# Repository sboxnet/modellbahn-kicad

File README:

modellbahn-kicad

KICAD schemas and Pcbs for modellbahn.

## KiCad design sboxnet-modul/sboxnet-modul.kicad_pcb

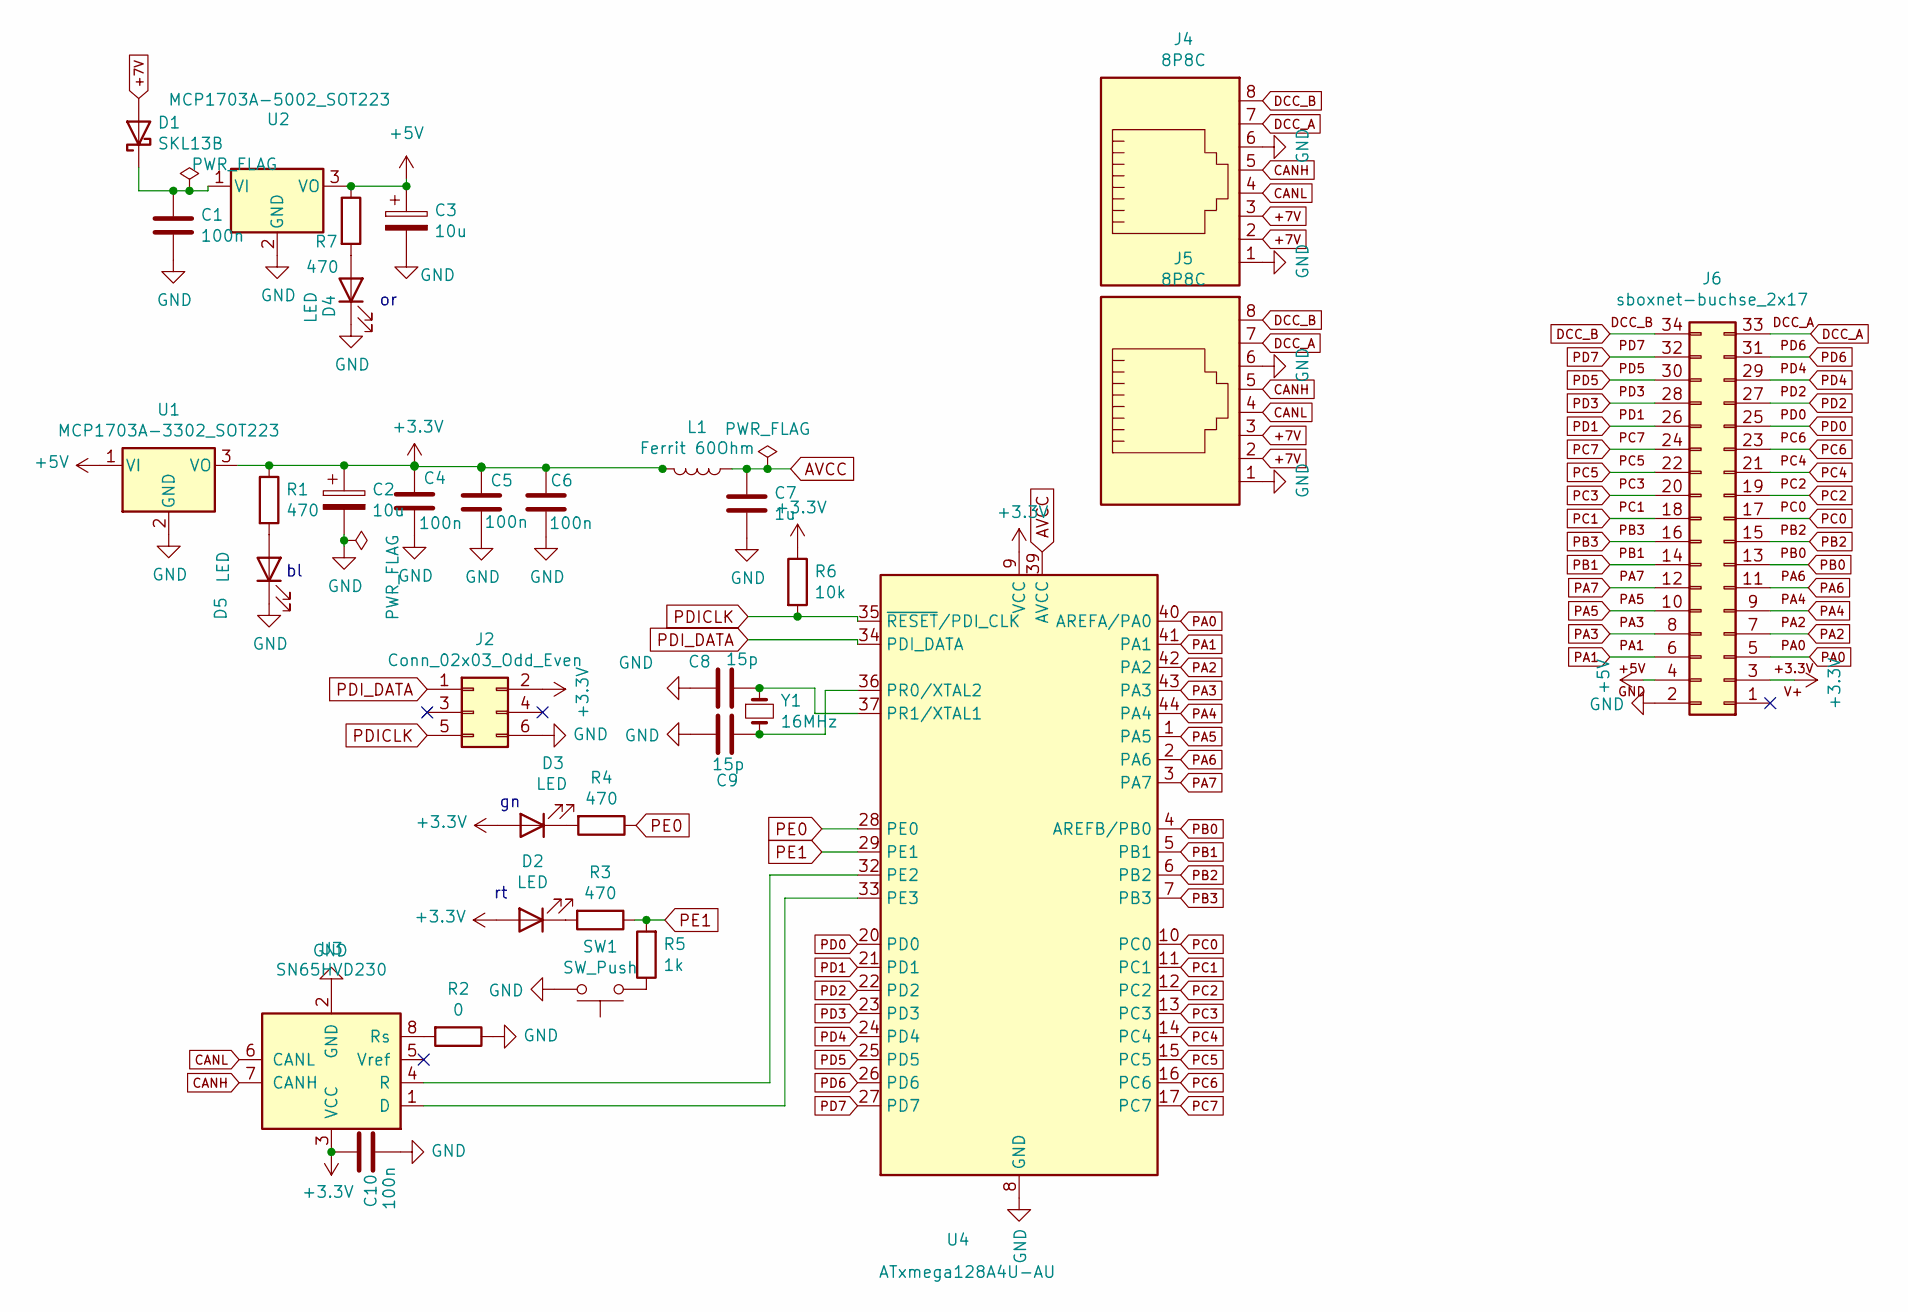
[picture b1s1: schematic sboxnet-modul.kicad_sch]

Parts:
C1, C4, C5, C6, C10: 100n; C_1206_3216Metric_Pad1.33x1.80mm_HandSolder
C2, C3: 10u; C_1206_3216Metric_Pad1.33x1.80mm_HandSolder
C7: 1u; C_1206_3216Metric_Pad1.33x1.80mm_HandSolder
C8, C9: 15p; C_1206_3216Metric_Pad1.33x1.80mm_HandSolder
D1: SKL13B; D_SMB_Handsoldering
D2, D3, D4, D5: LED; LED_1206_3216Metric_Pad1.42x1.75mm_HandSolder
J2: Conn_02x03_Odd_Even; wannenstecker_gerade_6pin
J4, J5: 8P8C; 8p8c-mebp
J6: sboxnet-buchse_2x17; sboxnet-buchse-2x17
L1: Ferrit 60Ohm; L_1206_3216Metric_Pad1.42x1.75mm_HandSolder
R1, R3, R4, R7: 470; R_1206_3216Metric_Pad1.30x1.75mm_HandSolder
R2: 0; R_1206_3216Metric_Pad1.30x1.75mm_HandSolder
R5: 1k; R_1206_3216Metric_Pad1.30x1.75mm_HandSolder
R6: 10k; R_1206_3216Metric_Pad1.30x1.75mm_HandSolder
SW1: SW_Push; JTP-1130
U1: MCP1703A-3302_SOT223; SOT-223-3_TabPin2
U2: MCP1703A-5002_SOT223; SOT-223-3_TabPin2
U3: SN65HVD230; SOIC-8_3.9x4.9mm_P1.27mm
U4: ATxmega128A4U-AU; TQFP-44_10x10mm_P0.8mm
Y1: 16MHz; Crystal_HC49-U_Vertical

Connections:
+3.3V: C2.1, C4.2, C5.2, C6.2, C10.2, D2.2 (A), D3.2 (A), J2.2, J6.3, L1.2, R1.1, R6.1, U1.3 (VO), U3.3 (VCC), U4.9 (VCC), U4.19 (VCC), U4.31 (VCC); also elsewhere on the board
+5V: C3.1, J6.4, R7.1, U1.1 (VI), U2.3 (VO); also elsewhere on the board
+7V: D1.2 (A), J4.2, J4.3, J5.2, J5.3
+V: J6.1
AVCC: C7.2, L1.1, U4.39 (AVCC)
CANH: J4.5, J5.5, U3.7 (CANH)
CANL: J4.4, J5.4, U3.6 (CANL)
DCC_A: J4.7, J5.7, J6.33
DCC_B: J4.8, J5.8, J6.34
GND: C1.1, C2.2, C3.2, C4.1, C5.1, C6.1, C7.1, C8.2, C9.2, C10.1, D4.1 (K), D5.1 (K), J2.6, J4.1, J4.6, J5.1, J5.6, J6.2, R2.1, SW1.2, U1.2 (GND), U2.2 (GND), U3.2 (GND), U4.8 (GND), U4.18 (GND), U4.30 (GND), U4.38 (GND); also elsewhere on the board
unnamed 10: C1.2, D1.1 (K), U2.1 (VI); also elsewhere on the board
unnamed: C8.1, U4.37 (PR1/XTAL1), Y1.1
unnamed: C9.1, U4.36 (PR0/XTAL2), Y1.2
unnamed: D2.1 (K), R3.2
unnamed: D3.1 (K), R4.2
unnamed: D4.2 (A), R7.2
unnamed: D5.2 (A), R1.2
unnamed: R2.2, U3.8 (Rs)
unnamed: R5.1, SW1.1
unnamed: U3.1 (D), U4.33 (PE3)
unnamed: U3.4 (R), U4.32 (PE2)
PA0: J6.5, U4.40 (AREFA/PA0)
PA1: J6.6, U4.41 (PA1)
PA2: J6.7, U4.42 (PA2)
PA3: J6.8, U4.43 (PA3)
PA4: J6.9, U4.44 (PA4)
PA5: J6.10, U4.1 (PA5)
PA6: J6.11, U4.2 (PA6)
PA7: J6.12, U4.3 (PA7)
PB0: J6.13, U4.4 (AREFB/PB0)
PB1: J6.14, U4.5 (PB1)
PB2: J6.15, U4.6 (PB2)
PB3: J6.16, U4.7 (PB3)
PC0: J6.17, U4.10 (PC0)
PC1: J6.18, U4.11 (PC1)
PC2: J6.19, U4.12 (PC2)
PC3: J6.20, U4.13 (PC3)
PC4: J6.21, U4.14 (PC4)
PC5: J6.22, U4.15 (PC5)
PC6: J6.23, U4.16 (PC6)
PC7: J6.24, U4.17 (PC7)
PD0: J6.25, U4.20 (PD0)
PD1: J6.26, U4.21 (PD1)
PD2: J6.27, U4.22 (PD2)
PD3: J6.28, U4.23 (PD3)
PD4: J6.29, U4.24 (PD4)
PD5: J6.30, U4.25 (PD5)
PD6: J6.31, U4.26 (PD6)
PD7: J6.32, U4.27 (PD7)
PDICLK: J2.5, R6.2, U4.35 (~RESET/PDI_CLK)
PDI_DATA: J2.1, U4.34 (PDI_DATA)
PE0: R4.1, U4.28 (PE0)
PE1: R3.1, R5.2, U4.29 (PE1)

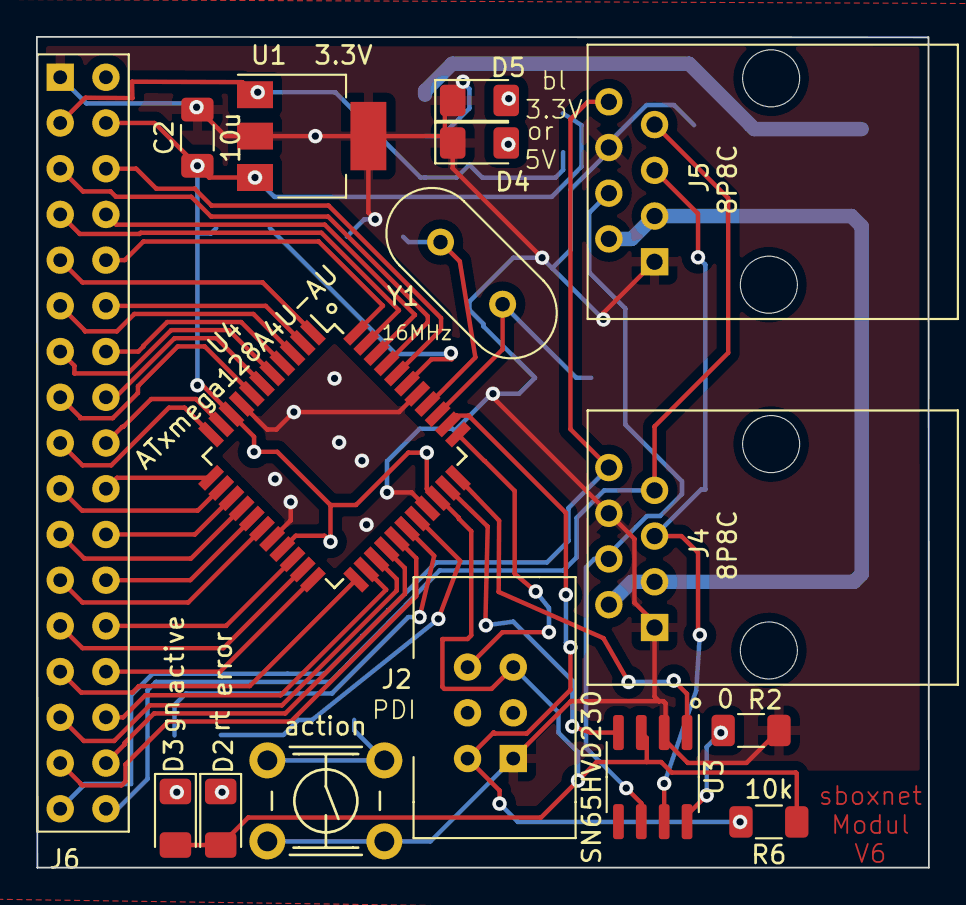
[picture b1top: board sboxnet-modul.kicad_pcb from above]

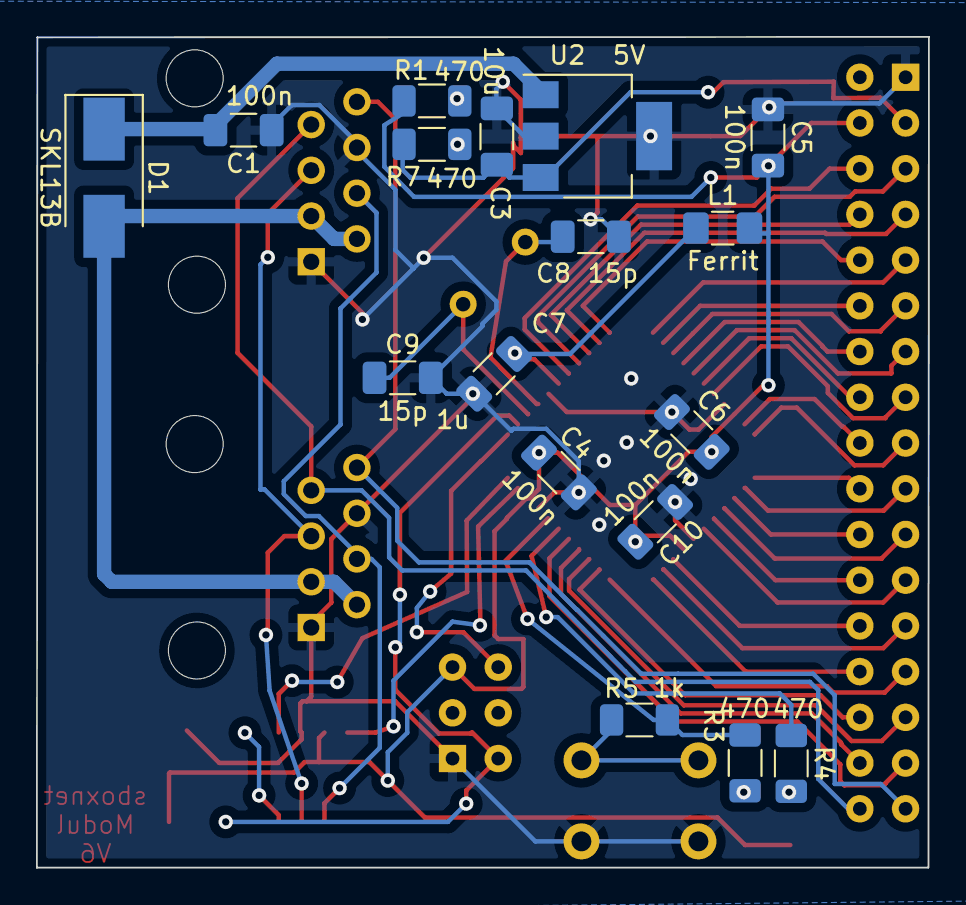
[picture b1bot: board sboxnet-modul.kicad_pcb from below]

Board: 2 copper layers, 49.6 x 46.2 mm, 33 parts (17 on the bottom side), 52 nets.

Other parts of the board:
U1  3.3V: MCP1703A-3302_SOT223; SOT-223-3_TabPin2
U2  5V: MCP1703A-5002_SOT223; SOT-223-3_TabPin2

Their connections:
+3.3V: U1 3.3V.3 (VO); also elsewhere on the board
+5V: U1 3.3V.1 (VI), U2 5V.3 (VO); also elsewhere on the board
GND: U1 3.3V.2 (GND), U2 5V.2 (GND); also elsewhere on the board
unnamed 10: U2 5V.1 (VI); also elsewhere on the board

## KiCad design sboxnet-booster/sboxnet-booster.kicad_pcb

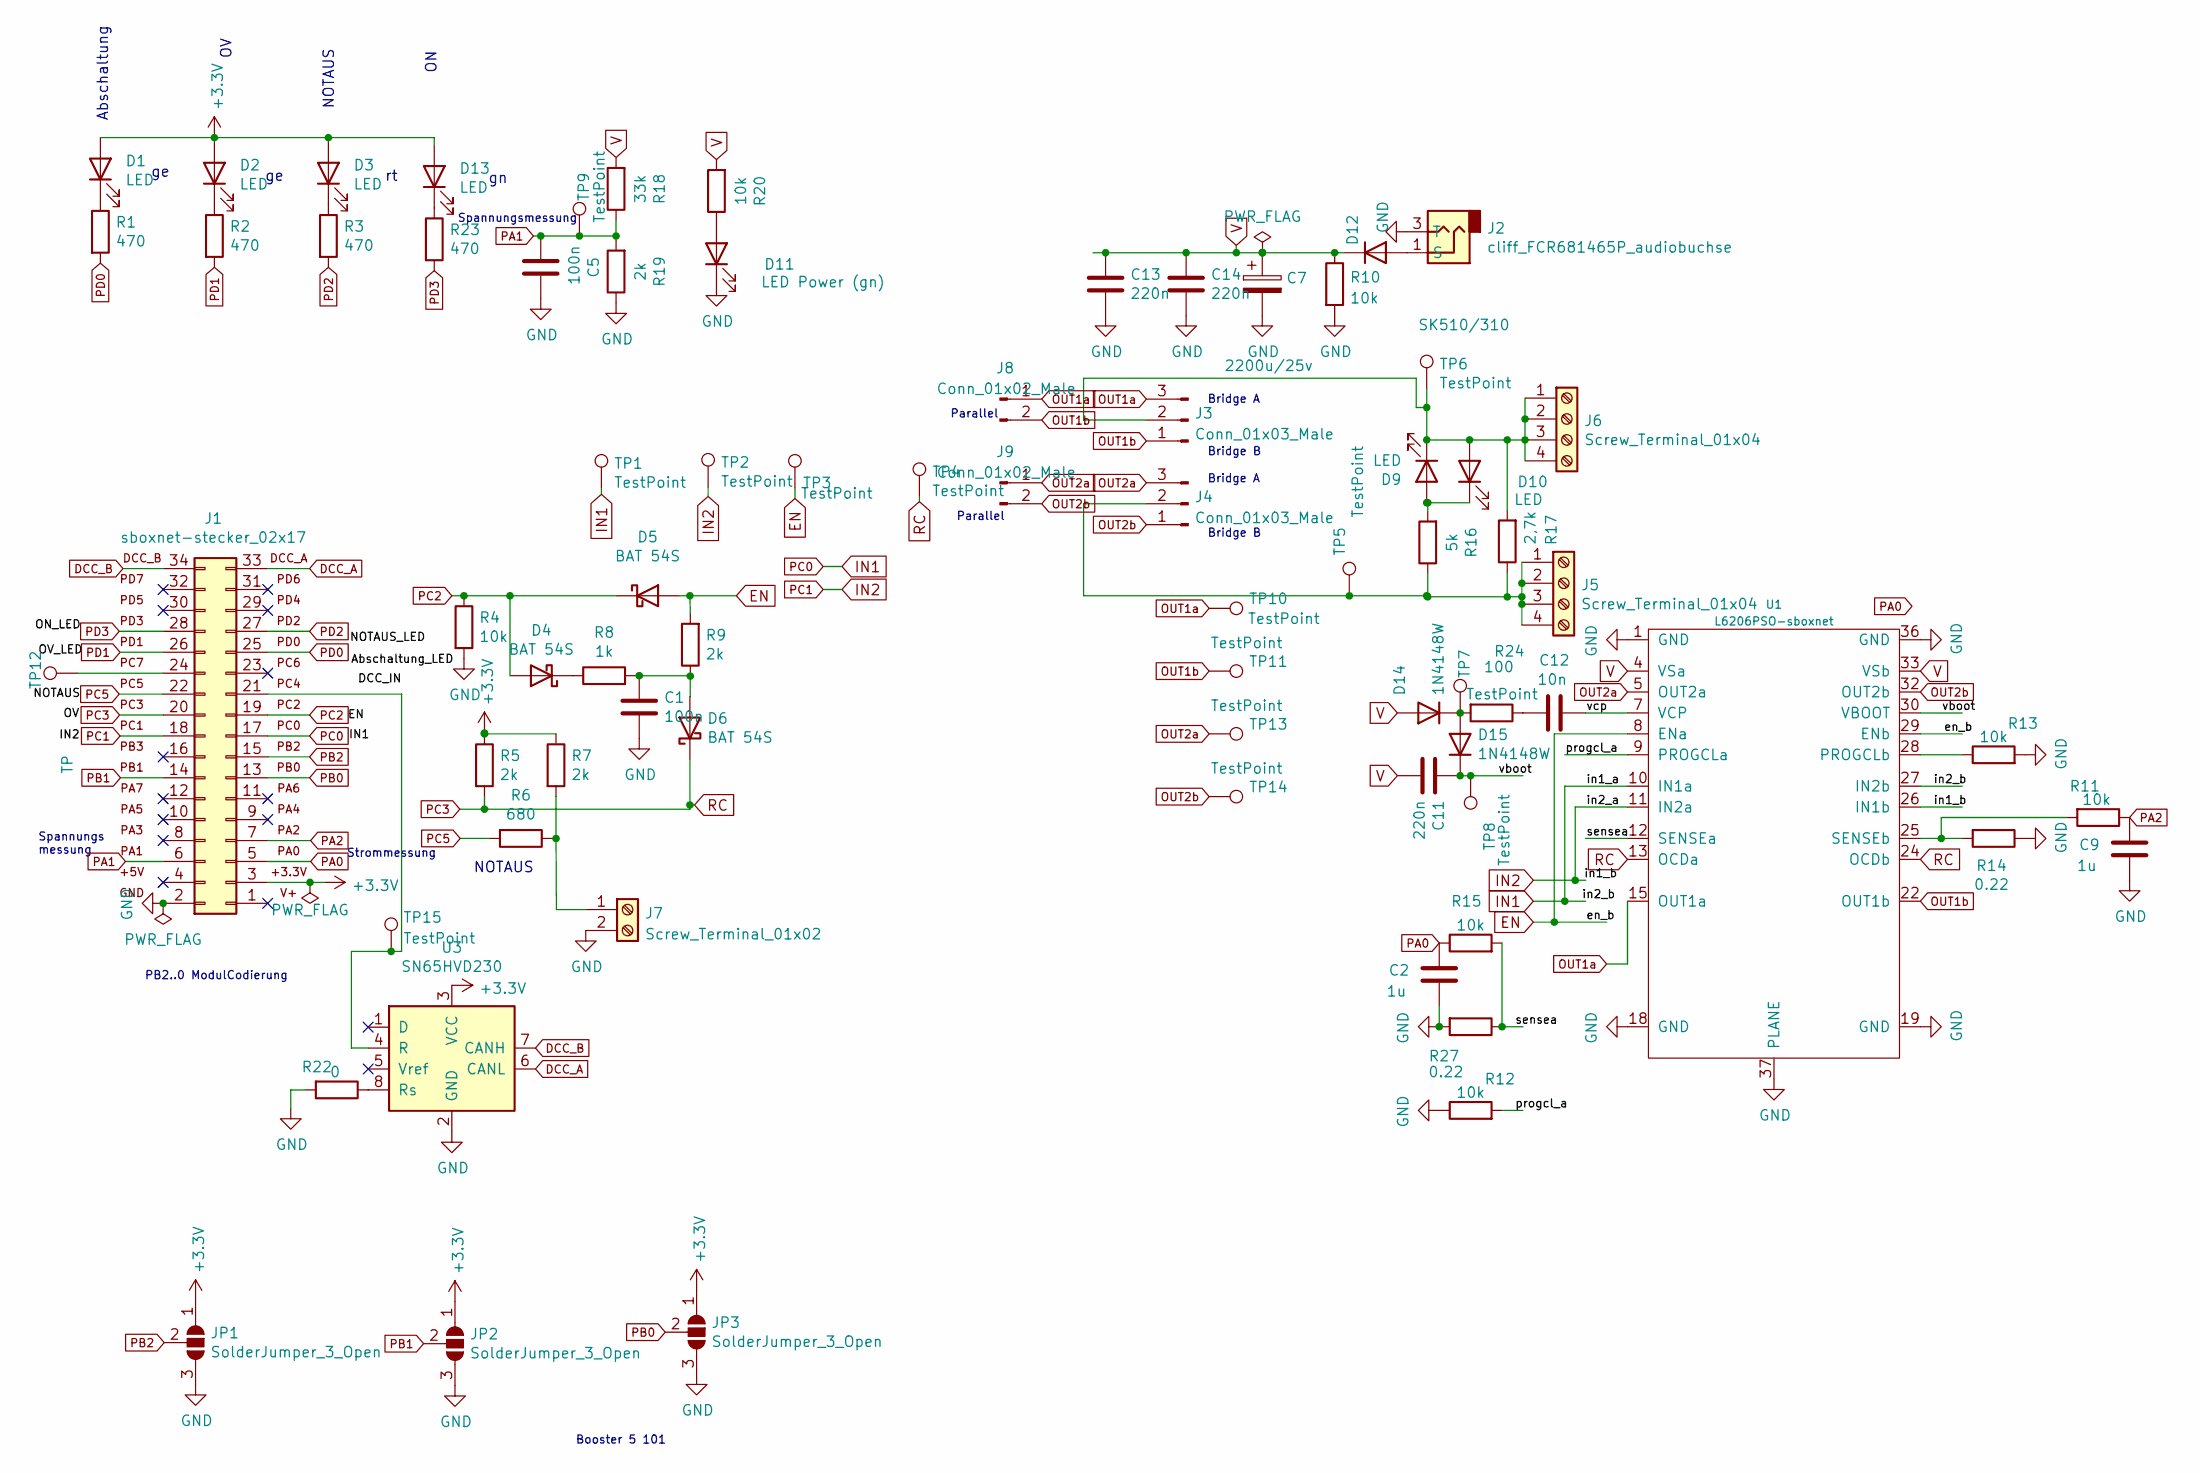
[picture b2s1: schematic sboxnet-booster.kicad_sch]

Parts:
C1, C5: 100n; C_1206_3216Metric
C2, C9: 1u; C_1206_3216Metric
C7: 2200u/25v; CP_Axial_L30.0mm_D15.0mm_P35.00mm_Horizontal
C11, C13, C14: 220n; C_1206_3216Metric
C12: 10n; C_1206_3216Metric
D1, D2, D3, D9, D10, D13: LED; LED_D3.0mm
D4, D5, D6: BAT 54S; SOT-23_Handsoldering
D11: LED Power (gn); LED_D3.0mm
D12: SK510/310; D_SMB_Handsoldering
D14, D15: 1N4148W; D_SOD-123F
J1: sboxnet-stecker_02x17; sboxnet-stecker-2x17
J2: cliff_FCR681465P_audiobuchse; CLIFF-FCR681465P
J3, J4: Conn_01x03_Male; PinHeader_1x03_P2.54mm_Vertical
J5, J6: Screw_Terminal_01x04; TerminalBlock_Altech_AK300-4_P5.00mm
J7: Screw_Terminal_01x02; TerminalBlock_Altech_AK300-2_P5.00mm
J8, J9: Conn_01x02_Male; PinHeader_1x02_P2.54mm_Vertical
JP1, JP2, JP3: SolderJumper_3_Open; SolderJumper-3_P1.3mm_Open_RoundedPad1.0x1.5mm
R1, R2, R3, R23: 470; R_1206_3216Metric_Pad1.30x1.75mm_HandSolder
R4, R10, R11, R12, R13, R15, R20: 10k; R_1206_3216Metric_Pad1.30x1.75mm_HandSolder
R5, R7, R9, R19: 2k; R_1206_3216Metric_Pad1.30x1.75mm_HandSolder
R6: 680; R_1206_3216Metric_Pad1.30x1.75mm_HandSolder
R8: 1k; R_1206_3216Metric_Pad1.30x1.75mm_HandSolder
R14, R27: 0.22; R_Axial_DIN0614_L14.3mm_D5.7mm_P15.24mm_Horizontal
R16: 5k; R_1206_3216Metric_Pad1.30x1.75mm_HandSolder
R17: 2,7k; R_1206_3216Metric_Pad1.30x1.75mm_HandSolder
R18: 33k; R_1206_3216Metric_Pad1.30x1.75mm_HandSolder
R22: 0; R_1206_3216Metric_Pad1.30x1.75mm_HandSolder
R24: 100; R_1206_3216Metric_Pad1.30x1.75mm_HandSolder
TP1, TP2, TP3, TP4, TP5, TP6, TP7, TP8, TP9, TP10, TP11, TP13, TP14, TP15: TestPoint; PinHeader_1x01_P2.54mm_Vertical
TP12: TP; PinHeader_1x01_P2.54mm_Vertical
U1: L6206PSO-sboxnet; HSOP-36-1EP_11.0x15.9mm_P0.65mm_SlugDown_ThermalVias
U3: SN65HVD230; SOIC-8_3.9x4.9mm_P1.27mm

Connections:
+3V3: D1.2 (A), D2.2 (A), D3.2 (A), D13.2 (A), J1.3, JP1.1 (A), JP2.1 (A), JP3.1 (A), R5.1, R7.1, U3.3 (VCC)
/progcl_a: R12.2, U1.9 (PROGCLa)
/sensea: R15.2, R27.1, U1.12 (SENSEa)
/vboot: C11.2, D15.1 (K), TP8.1, U1.30 (VBOOT)
/vcp: C12.1, U1.7 (VCP)
DCC_A: J1.33, U3.6 (CANL)
DCC_B: J1.34, U3.7 (CANH)
EN: D5.1 (A), R9.2, TP3.1, U1.8 (ENa), U1.29 (ENb)
GND: C1.2, C2.1, C5.1, C7.2, C9.1, C13.1, C14.1, D11.1 (K), J1.2, J2.3 (T), J7.2, JP1.3 (B), JP2.3 (B), JP3.3 (B), R4.2, R10.2, R12.1, R13.2, R14.1, R19.1, R22.2, R27.2, U1.1 (GND), U1.18 (GND), U1.19 (GND), U1.36 (GND), U1.37 (PLANE), U3.2 (GND)
unnamed: C1.1, D6.1 (A), R8.2, R9.1
unnamed: C12.2, R24.1
unnamed: D1.1 (K), R1.1
unnamed: D2.1 (K), R2.1
unnamed: D3.1 (K), R3.1
unnamed: D4.3 (K), R8.1
unnamed: D9.2 (A), D10.1 (K), R16.2
unnamed: D9.1 (K), D10.2 (A), J3.2, J6.1, J6.2, J6.3, J6.4, R17.2, TP6.1
unnamed: D11.2 (A), R20.1
unnamed: D12.2 (A), J2.1 (S)
unnamed: D13.1 (K), R23.1
unnamed: D14.1 (K), D15.2 (A), R24.2, TP7.1
unnamed: J1.21, TP15.1, U3.4 (R)
unnamed: J1.24, TP12.1
unnamed: J4.2, J5.1, J5.2, J5.3, J5.4, R16.1, R17.1, TP5.1
unnamed: J7.1, R6.1, R7.2
unnamed: R11.2, R14.2, U1.25 (SENSEb)
unnamed: R13.1, U1.28 (PROGCLb)
unnamed: R22.1, U3.8 (Rs)
OUT1a: J3.3, J8.1, TP10.1, U1.15 (OUT1a)
OUT1b: J3.1, J8.2, TP11.1, U1.22 (OUT1b)
OUT2a: J4.3, J9.1, TP13.1, U1.5 (OUT2a)
OUT2b: J4.1, J9.2, TP14.1, U1.32 (OUT2b)
PA0: C2.2, J1.5, R15.1
PA1: C5.2, J1.6, R18.1, R19.2, TP9.1
PA2: C9.2, J1.7, R11.1
PB0: J1.13, JP3.2 (C)
PB1: J1.14, JP2.2 (C)
PB2: J1.15, JP1.2 (C)
PC2: D4.1 (A), D5.3 (K), J1.19, R4.1
PC3: D6.3 (K), J1.20, R5.2, TP4.1, U1.13 (OCDa), U1.24 (OCDb)
PC5: J1.22, R6.2
PD0: J1.25, R1.2
PD1: J1.26, R2.2
PD2: J1.27, R3.2
PD3: J1.28, R23.2
V: C7.1, C11.1, C13.2, C14.2, D12.1 (K), D14.2 (A), R10.1, R18.2, R20.2, U1.4 (VSa), U1.33 (VSb)

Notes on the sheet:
NOTAUS
Bridge B
Abschaltung
Bridge A
Booster 5 101
Spannungs messung
Spannungsmessung
Strommessung
Parallel
PB2..0 ModulCodierung

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
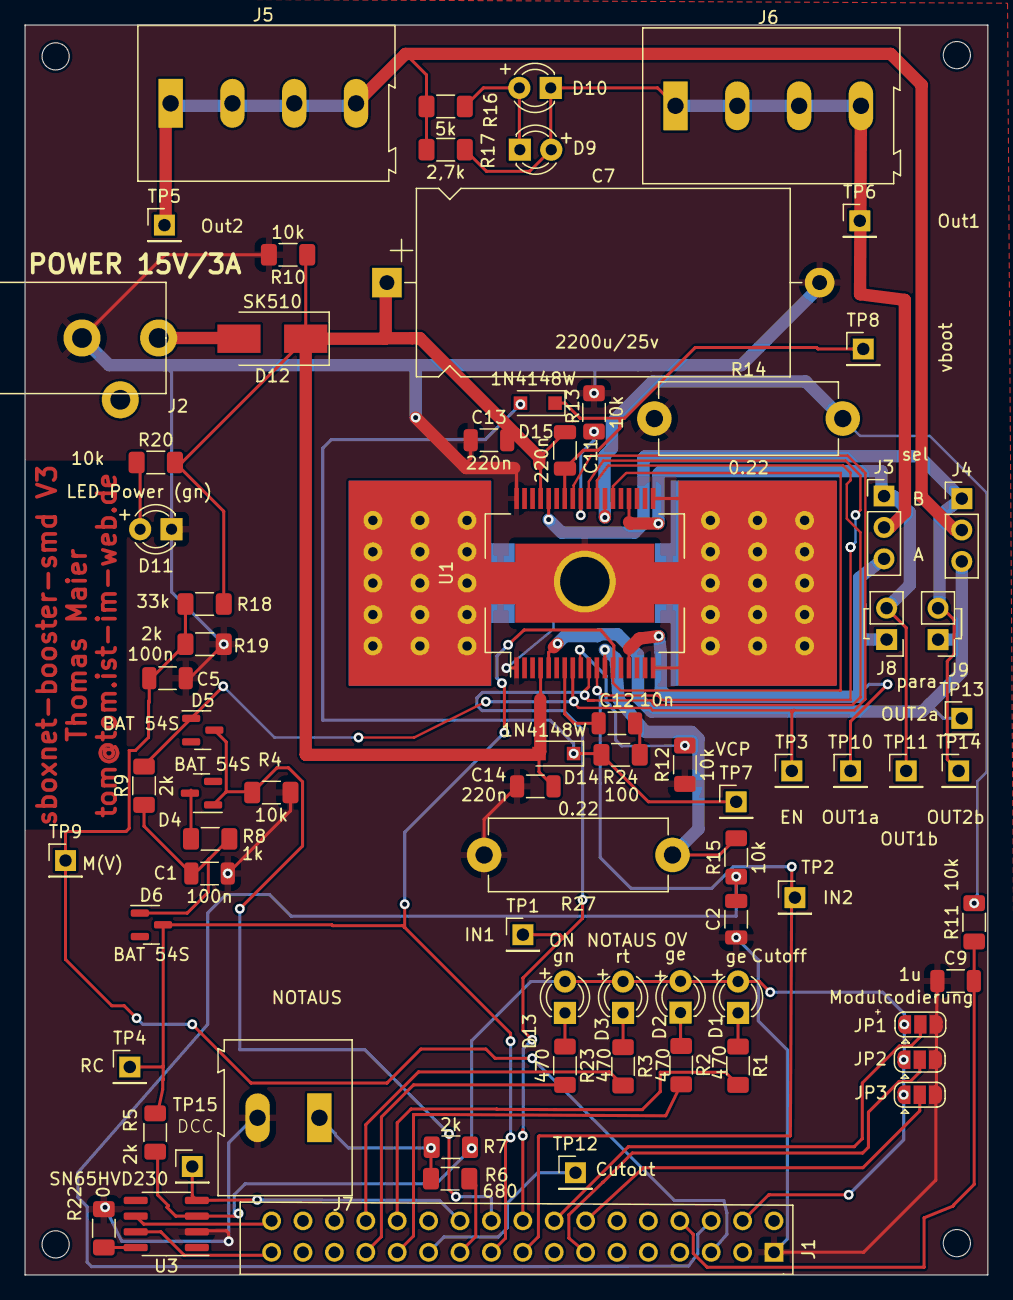
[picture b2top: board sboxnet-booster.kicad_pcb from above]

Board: 2 copper layers, 77.9 x 101.1 mm, 75 parts (0 on the bottom side), 48 nets.

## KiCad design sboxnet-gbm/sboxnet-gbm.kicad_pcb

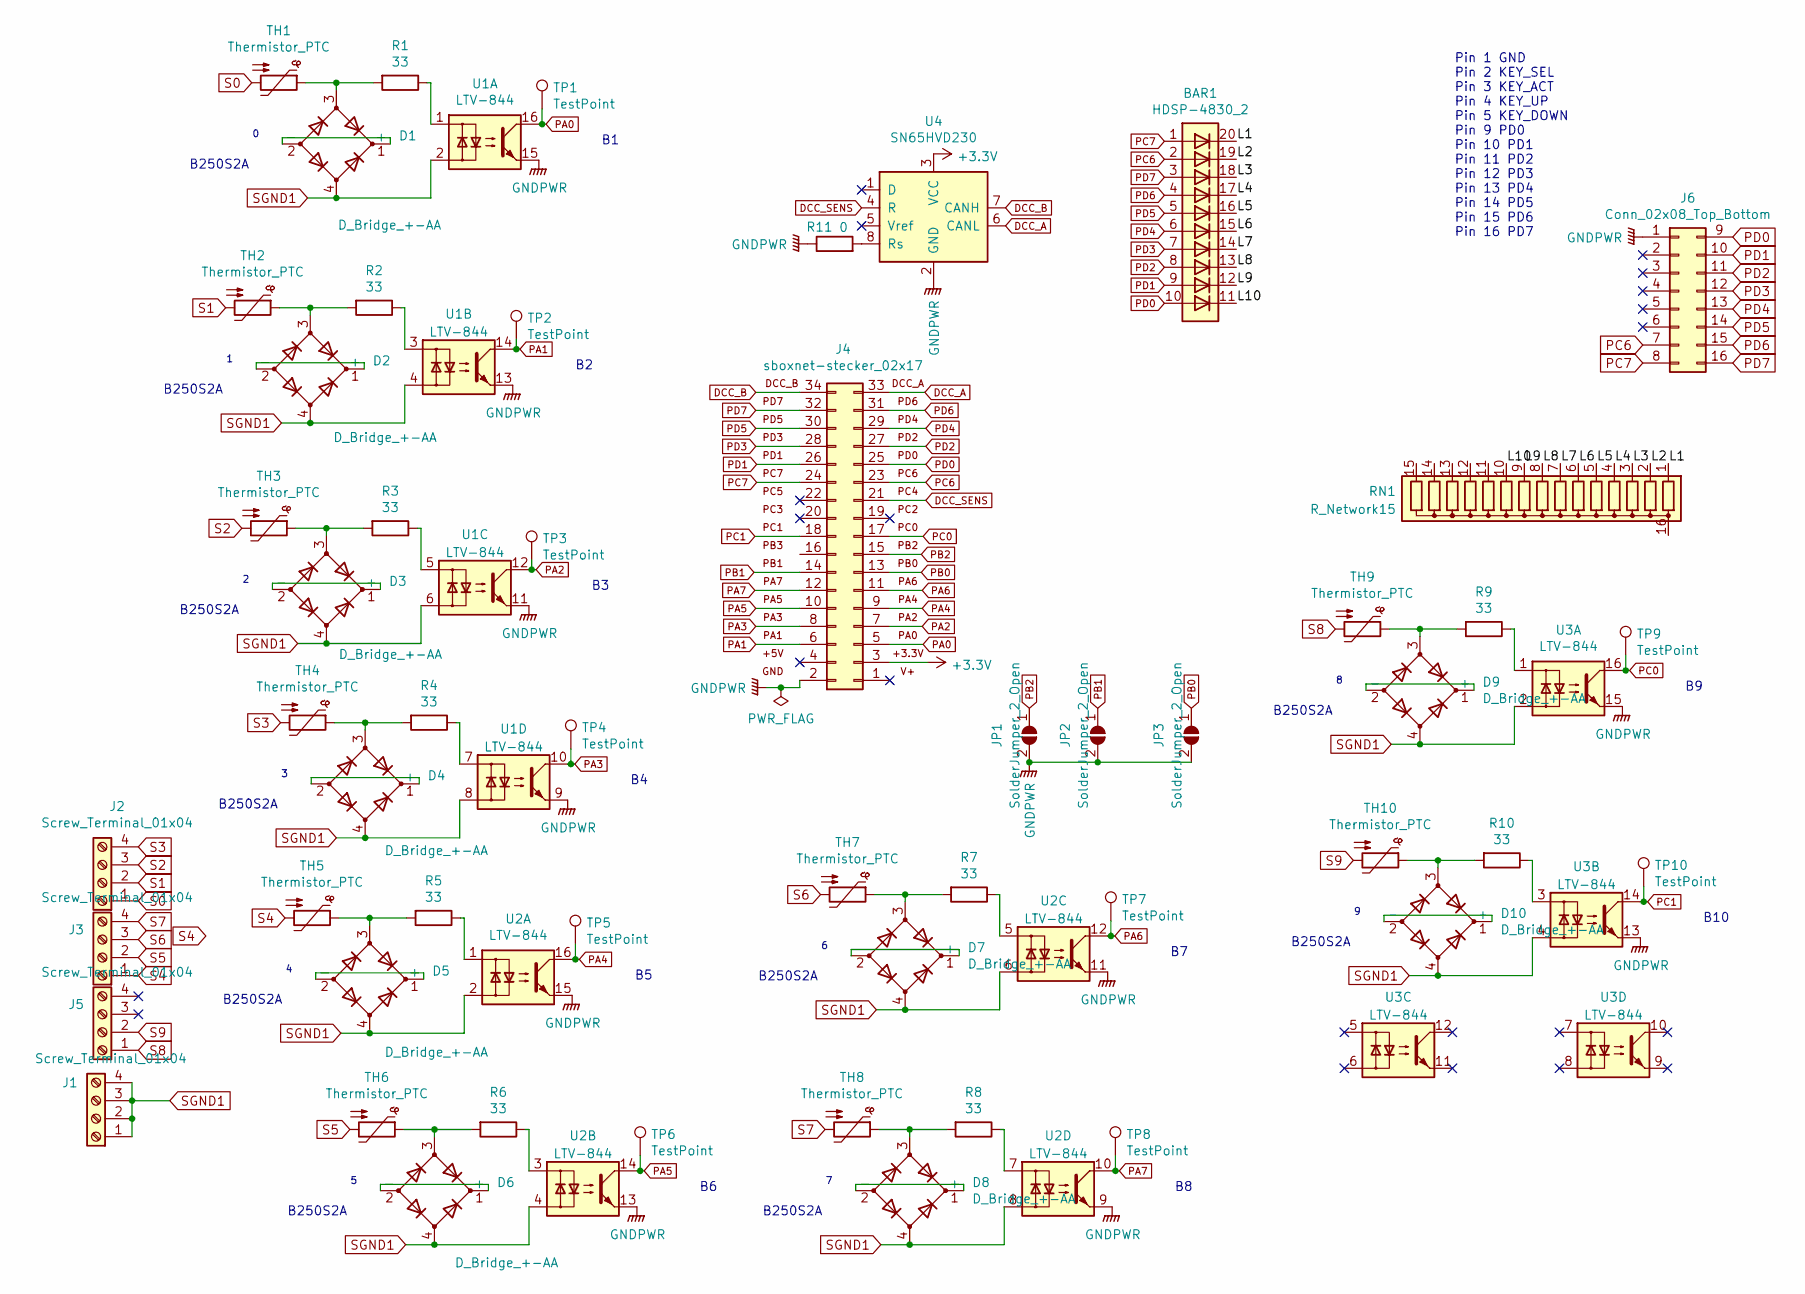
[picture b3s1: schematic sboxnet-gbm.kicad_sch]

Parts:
BAR1: HDSP-4830_2; DIP-20_W7.62mm_Socket
D1, D2, D3, D4, D5, D6, D7, D8, D9, D10: D_Bridge_+-AA; Diode_Bridge_Diotec_SO-DIL-Slim
J1, J2, J3, J5: Screw_Terminal_01x04; TerminalBlock_Altech_AK300-4_P5.00mm
J4: sboxnet-stecker_02x17; sboxnet-stecker-2x17
J6: Conn_02x08_Top_Bottom; PinSocket_2x08_P2.54mm_Vertical
JP1, JP2, JP3: SolderJumper_2_Open; SolderJumper-2_P1.3mm_Open_TrianglePad1.0x1.5mm
R1, R2, R3, R4, R5, R6, R7, R8, R9, R10: 33; R_1206_3216Metric_Pad1.30x1.75mm_HandSolder
R11: 0; R_1206_3216Metric_Pad1.30x1.75mm_HandSolder
RN1: R_Network15; SOIC-16W_5.3x10.2mm_P1.27mm
TH1, TH2, TH3, TH4, TH5, TH6, TH7, TH8, TH9, TH10: Thermistor_PTC; R_1206_3216Metric
TP1, TP2, TP3, TP4, TP5, TP6, TP7, TP8, TP9, TP10: TestPoint; PinHeader_1x01_P2.54mm_Vertical
U1, U2, U3: LTV-844; SOIC-16_4.55x10.3mm_P1.27mm
U4: SN65HVD230; SOIC-8_3.9x4.9mm_P1.27mm

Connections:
+3V3: J4.3, U4.3 (VCC)
/L1: BAR1.20 (K), RN1.1 (R1)
/L2: BAR1.19 (K), RN1.2 (R2)
/L3: BAR1.18 (K), RN1.3 (R3)
/L4: BAR1.17 (K), RN1.4 (R4)
/L5: BAR1.16 (K), RN1.5 (R5)
/L6: BAR1.15 (K), RN1.6 (R6)
/L7: BAR1.14 (K), RN1.7 (R7)
/L8: BAR1.13 (K), RN1.8 (R8)
/L9: BAR1.12 (K), RN1.9 (R9)
/L10: BAR1.11 (K), RN1.10 (R10)
DCC_A: J4.33, U4.6 (CANL)
DCC_B: J4.34, U4.7 (CANH)
DCC_SENS: J4.21, U4.4 (R)
GNDPWR: J4.2, J6.1, JP1.2 (B), JP2.2 (B), JP3.2 (B), R11.1, U1.9, U1.11, U1.13, U1.15, U2.9, U2.11, U2.13, U2.15, U3.13, U3.15, U4.2 (GND)
unnamed: D1.1 (+), D1.2 (-)
unnamed: D1.3, R1.2, TH1.1
unnamed: D2.1 (+), D2.2 (-)
unnamed: D2.3, R2.2, TH2.1
unnamed: D3.1 (+), D3.2 (-)
unnamed: D3.3, R3.2, TH3.1
unnamed: D4.1 (+), D4.2 (-)
unnamed: D4.3, R4.2, TH4.1
unnamed: D5.1 (+), D5.2 (-)
unnamed: D5.3, R5.2, TH5.1
unnamed: D6.1 (+), D6.2 (-)
unnamed: D6.3, R6.2, TH6.1
unnamed: D7.1 (+), D7.2 (-)
unnamed: D7.3, R7.2, TH7.1
unnamed: D8.1 (+), D8.2 (-)
unnamed: D8.3, R8.2, TH8.1
unnamed: D9.1 (+), D9.2 (-)
unnamed: D9.3, R9.2, TH9.1
unnamed: D10.1 (+), D10.2 (-)
unnamed: D10.3, R10.2, TH10.1
unnamed: R1.1, U1.1
unnamed: R2.1, U1.3
unnamed: R3.1, U1.5
unnamed: R4.1, U1.7
unnamed: R5.1, U2.1
unnamed: R6.1, U2.3
unnamed: R7.1, U2.5
unnamed: R8.1, U2.7
unnamed: R9.1, U3.1
unnamed: R10.1, U3.3
unnamed: R11.2, U4.8 (Rs)
PA0: J4.5, TP1.1, U1.16
PA1: J4.6, TP2.1, U1.14
PA2: J4.7, TP3.1, U1.12
PA3: J4.8, TP4.1, U1.10
PA4: J4.9, TP5.1, U2.16
PA5: J4.10, TP6.1, U2.14
PA6: J4.11, TP7.1, U2.12
PA7: J4.12, TP8.1, U2.10
PB0: J4.13, JP3.1 (A)
PB1: J4.14, JP2.1 (A)
PB2: J4.15, JP1.1 (A)
PC0: J4.17, TP9.1, U3.16
PC1: J4.18, TP10.1, U3.14
PC6: BAR1.2 (A), J4.23, J6.7
PC7: BAR1.1 (A), J4.24, J6.8
PD0: BAR1.10 (A), J4.25, J6.9
PD1: BAR1.9 (A), J4.26, J6.10
PD2: BAR1.8 (A), J4.27, J6.11
PD3: BAR1.7 (A), J4.28, J6.12
PD4: BAR1.6 (A), J4.29, J6.13
PD5: BAR1.5 (A), J4.30, J6.14
PD6: BAR1.4 (A), J4.31, J6.15
PD7: BAR1.3 (A), J4.32 (PD7), J6.16
S0: J2.1, TH1.2
S1: J2.2, TH2.2
S2: J2.3, TH3.2
S3: J2.4, TH4.2
S4: J3.1, TH5.2
S5: J3.2, TH6.2
S6: J3.3, TH7.2
S7: J3.4, TH8.2
S8: J5.1, TH9.2
S9: J5.2, TH10.2
SGND1: D1.4, D2.4, D3.4, D4.4, D5.4, D6.4, D7.4, D8.4, D9.4, D10.4, J1.1, J1.2, J1.3, J1.4, U1.2, U1.4, U1.6, U1.8, U2.2, U2.4, U2.6, U2.8, U3.2, U3.4

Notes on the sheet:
B250S2A
Pin 1 GND Pin 2 KEY_SEL Pin 3 KEY_ACT Pin 4 KEY_UP Pin 5 KEY_DOWN Pin 9 PD0 Pin 10 PD1 Pin 11 PD2 Pin 12 PD3 Pin 13 PD4 Pin 14 PD5 Pin 15 PD6 Pin 16 PD7
B10

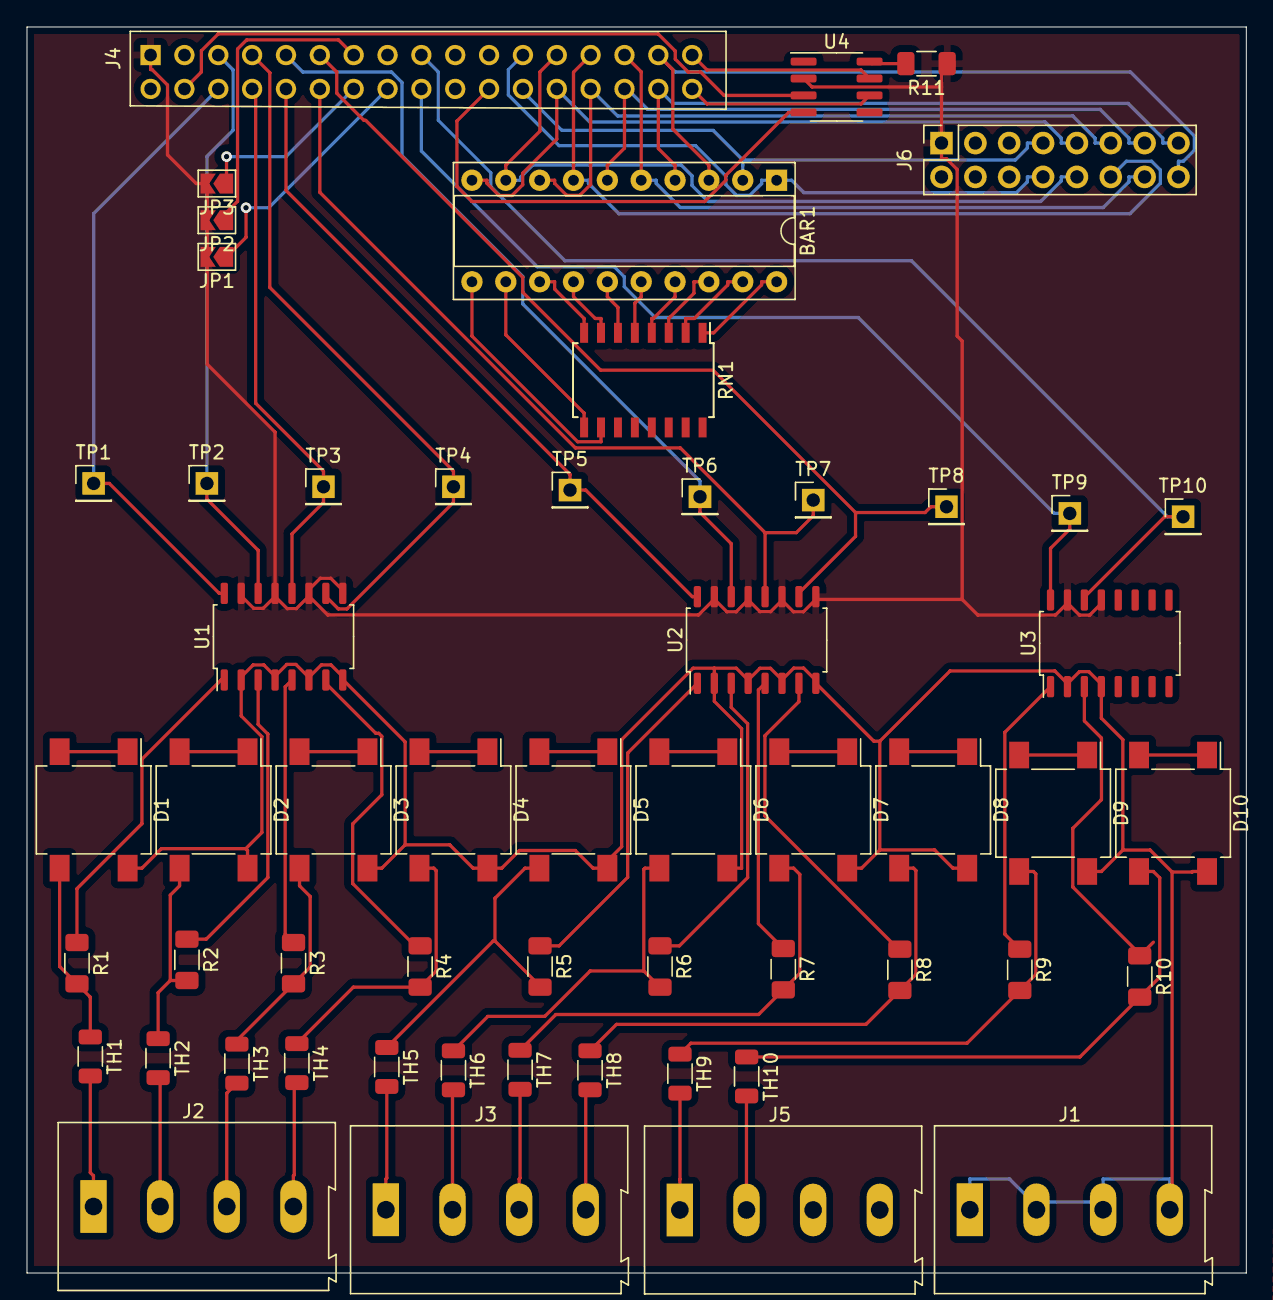
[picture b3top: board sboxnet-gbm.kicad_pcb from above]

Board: 2 copper layers, 91.5 x 93.5 mm, 56 parts (0 on the bottom side), 80 nets.

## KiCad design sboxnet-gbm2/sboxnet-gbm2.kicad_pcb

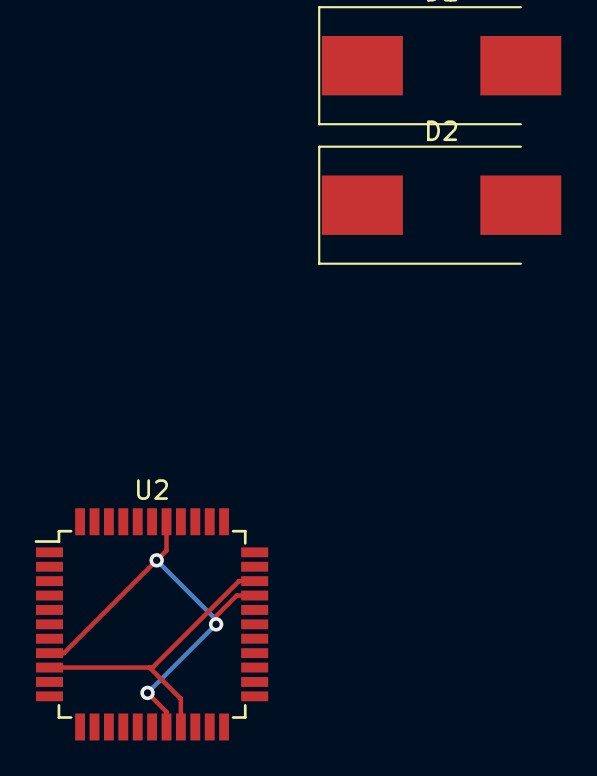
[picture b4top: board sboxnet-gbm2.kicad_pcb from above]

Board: 2 copper layers, 3 parts (0 on the bottom side), 3 nets.

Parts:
D1, D2: SB340; D_SMC_Handsoldering
U2: ATxmega32A4U-A; TQFP-44_10x10mm_P0.8mm

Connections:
+3.3VP: U2.9 (VCC), U2.19 (VCC), U2.31 (VCC)
/dcc1: D1.2 (A), D2.1 (K)
GND1: D1.1 (K), D2.2 (A), U2.8 (GND), U2.18 (GND), U2.30 (GND), U2.38 (GND)

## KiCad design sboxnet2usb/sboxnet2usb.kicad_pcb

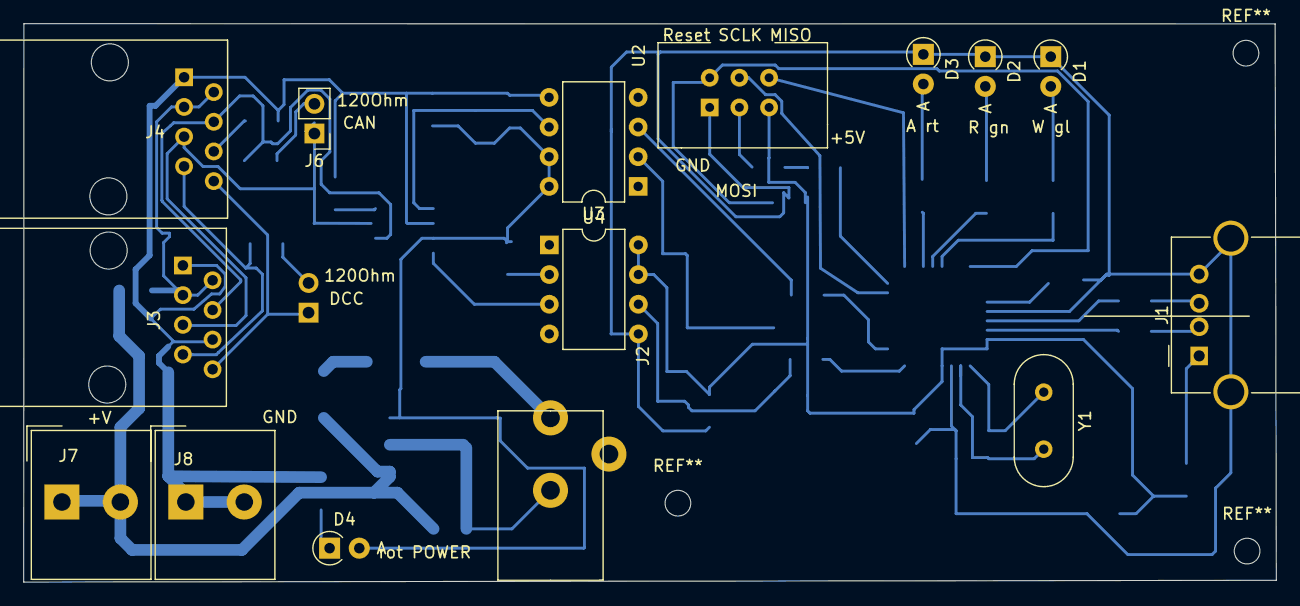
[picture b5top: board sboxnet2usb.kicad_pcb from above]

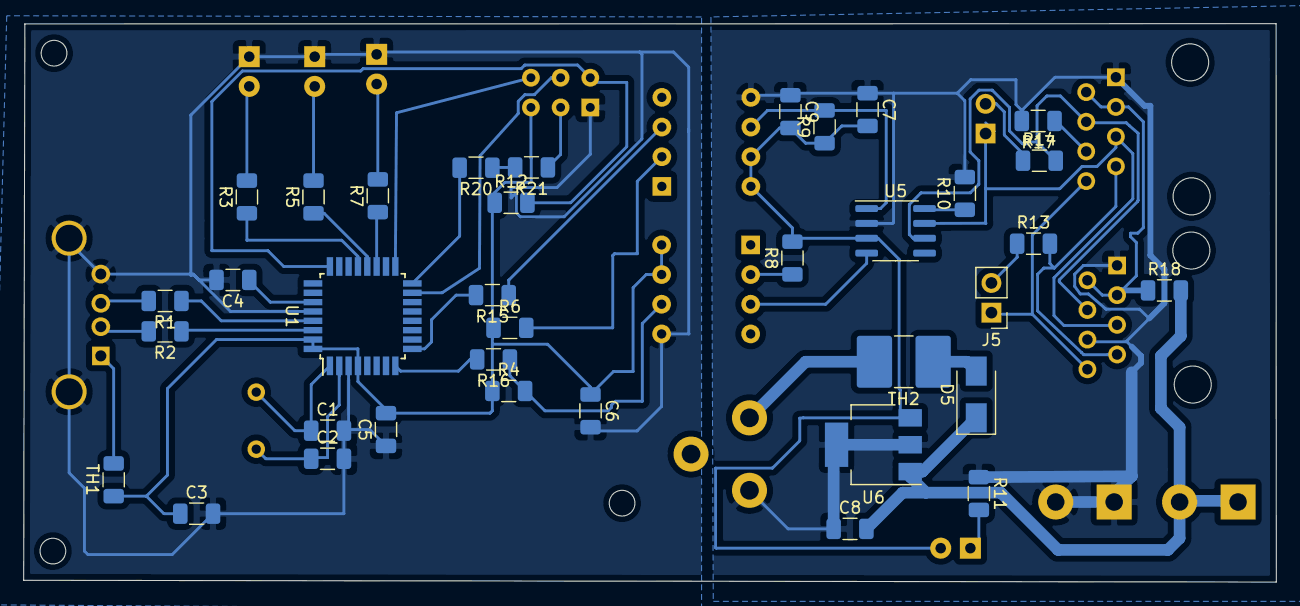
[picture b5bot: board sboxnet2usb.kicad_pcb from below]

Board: 2 copper layers, 107.2 x 47.8 mm, 51 parts (36 on the bottom side), 45 nets.

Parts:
C1, C2: 22p; C_1206_3216Metric
C3, C4: 1u; C_1206_3216Metric
C5, C6, C7, C8: 100n; C_1206_3216Metric
C9: 10u; C_1206_3216Metric
D1: gelb; D_A-405_P2.54mm_Vertical_AnodeUp
D2: grün; D_A-405_P2.54mm_Vertical_AnodeUp
D3, D4: rot; D_A-405_P2.54mm_Vertical_AnodeUp
D5: SK310A; D_SMA
J1: USB_A; USB_A_Molex_67643_Horizontal
J2: cliff_FCR681465P_audiobuchse; CLIFF-FCR681465P
J3, J4: 8P8C; 8p8c-mebp
J5, J6: Conn_01x02_Male; PinHeader_1x02_P2.54mm_Vertical
J7, J8: Screw_Terminal_01x02; Altech_AK300_1x02_P5.00mm_45-Degree
R1, R2: 22; R_1206_3216Metric
R3, R5, R7: 1k; R_1206_3216Metric
R4, R6, R8, R9, R11: 470; R_1206_3216Metric
R10, R15, R16, R17, R18, R20, R21: 0; R_1206_3216Metric
R12: 10k; R_1206_3216Metric
R13, R14: 120; R_1206_3216Metric
TH1: 250mA; R_1206_3216Metric
TH2: 3A; R_2816_7142Metric
U1: ATmega32U2-AU; TQFP-32_7x7mm_P0.8mm
U2: wannenstecker6; wannenstecker_gerade_6pin
U3, U4: 6N137; DIP-8_W7.62mm
U5: PCA82C250; SOIC-8_3.9x4.9mm_P1.27mm
U6: MCP1703A-5002_SOT223; SOT-223-3_TabPin2
Y1: 16MHz; Crystal_HC49-U_Vertical

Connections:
+5V: C3.1, C5.2, C6.1, R4.1, R6.1, R12.1, TH1.1, U1.4, U1.31, U1.32, U2.2, U4.7, U4.8
+5VP: C7.2, C9.2, D4.2, R8.2, R9.1, U3.7, U3.8, U5.3, U6.3
+9V: C8.2, D5.1, J7.1, J7.2, R18.2, U6.1
CANH: J3.5, J4.5, J6.1, U5.7
CANL: J3.4, J4.4, R14.2, U5.6
DCC_A: J3.7, J4.7, R13.2
DCC_B: J3.8, J4.8, J5.1
GND: C1.2, C2.2, C3.2, C4.2, C5.1, C6.2, D1.1, D2.1, D3.1, J1.4, J1.5, U1.3, U1.28, U2.6, U4.5
GND1: C7.1, C8.1, C9.1, J2.3, J3.1, J3.6, J4.1, J8.1, J8.2, R10.2, R11.1, R17.2, U3.5, U5.2, U6.2
LED_gl: R3.1, U1.21
LED_gn: R5.1, U1.20
LED_rt: R7.1, U1.19
MISO: U1.17, U2.1
MOSI: R21.1, U2.4
unnamed: C1.1, U1.1, Y1.1
unnamed: C2.1, U1.2, Y1.2
unnamed: C4.1, U1.27
unnamed: D1.2, R3.2
unnamed: D2.2, R5.2
unnamed: D3.2, R7.2
unnamed: D4.1, R11.2
unnamed: D5.2, TH2.1
unnamed: J1.1, TH1.2
unnamed: J1.2, R2.2
unnamed: J1.3, R1.2
unnamed: J2.1, TH2.2
unnamed: J3.2, J3.3, J4.2, J4.3, R18.1
unnamed: J4.6, R17.1
unnamed: J5.2, R13.1
unnamed: J6.2, R14.1
unnamed: R1.1, U1.29
unnamed: R2.1, U1.30
unnamed: R6.2, U3.2
unnamed: R8.1, U4.2
unnamed: R10.1, U5.8
unnamed: R15.1, U3.3
unnamed: R4.2, R16.1, U4.6
unnamed: R20.1, R21.2
unnamed: R20.2, U1.16
R: U4.3, U5.4
RESET: R12.2, U1.24, U2.5
RXD1: R16.2, U1.8
SCLK: U1.15, U2.3
T: R9.2, U3.6, U5.1
TXD1: R15.2, U1.9
